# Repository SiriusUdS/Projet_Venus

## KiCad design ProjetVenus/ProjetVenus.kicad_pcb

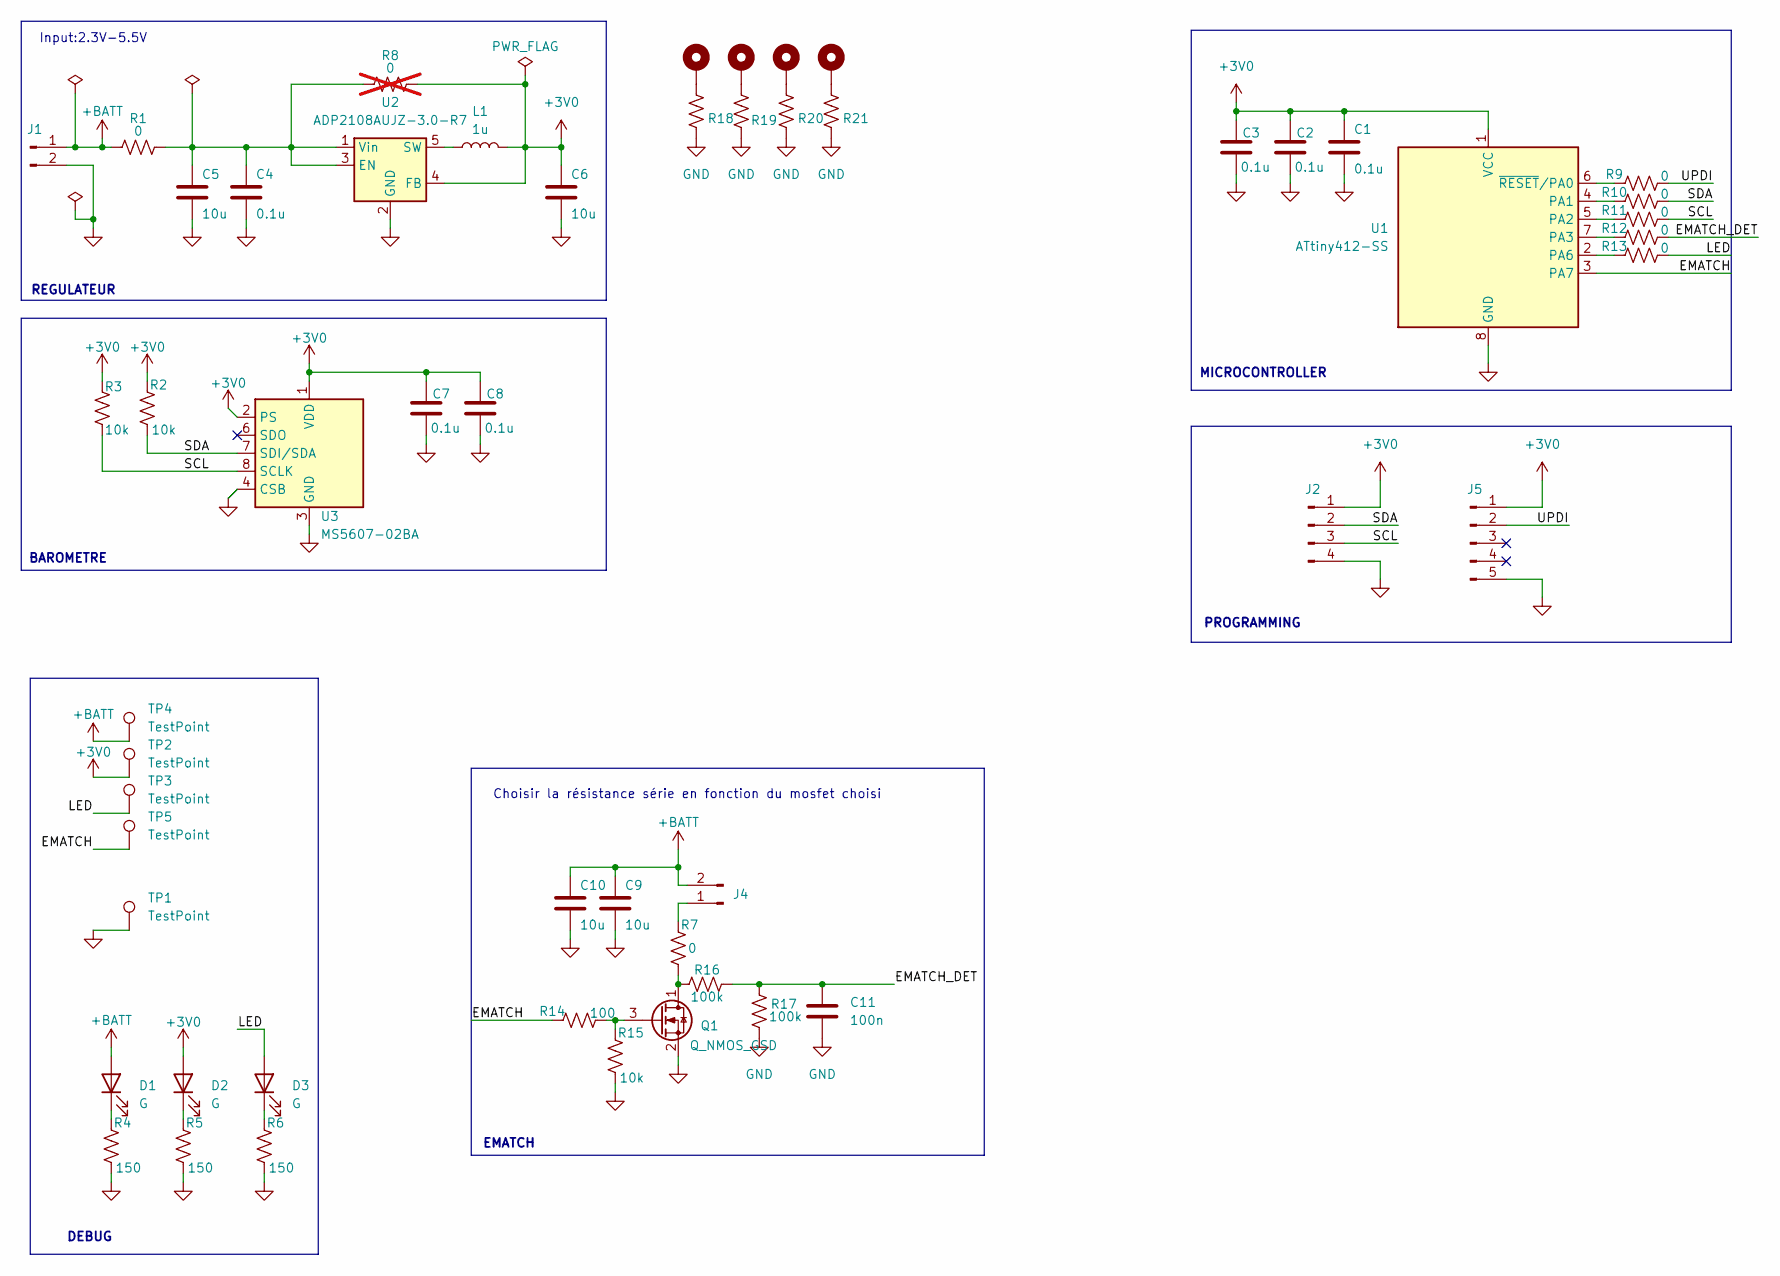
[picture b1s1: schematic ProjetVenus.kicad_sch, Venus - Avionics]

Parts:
C1, C2, C3, C4, C7, C8: 0.1u; C_0603_1608Metric
C5, C6, C9, C10: 10u; C_1206_3216Metric
C11: 100n; C_0603_1608Metric
D1, D2, D3: G; LED_0603_1608Metric
H1, H2, H3, H4: MountingHole_Pad; MountingHole_3.2mm_M3_DIN965_Pad
J1: Conn_01x02_Pin; Hirose_DF13-02P-1.25DS_1x02_P1.25mm_Horizontal
J2: Conn_01x04_Pin; PinSocket_1x04_P2.54mm_Vertical
J4: Conn_01x02_Pin; TerminalBlock_Phoenix_MKDS-1,5-2_1x02_P5.00mm_Horizontal
J5: Conn_01x05_Pin; PinSocket_1x05_P2.54mm_Vertical
L1: 1u; L_0805_2012Metric
Q1: Q_NMOS_GSD; SOT-23
R1, R9, R10, R11, R12, R13: 0; R_0805_2012Metric
R2, R3, R15: 10k; R_0603_1608Metric
R4, R5, R6: 150; R_0603_1608Metric
R7: 0; R_0603_1608Metric
R8: 0; R_0805_2012Metric; not fitted
R14: 100; R_0805_2012Metric
R16, R17: 100k; R_0603_1608Metric
R18, R19, R20, R21: R_US; R_0805_2012Metric
TP1: TestPoint; TestPoint_Pad_2.0x2.0mm
TP2, TP3, TP4, TP5: TestPoint; TestPoint_Pad_D2.0mm
U1: ATtiny412-SS; SOIC-8_3.9x4.9mm_P1.27mm
U2: ADP2108AUJZ-3.0-R7; TSOT-23-5
U3: MS5607-02BA; LGA-8_3x5mm_P1.25mm

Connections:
+3V0: C1.1, C2.1, C3.1, C6.1, C7.1, C8.1, D2.2 (A), J2.1, J5.1, L1.2, R2.2, R3.2, R8.2, TP2.1 (1_1), U1.1 (VCC), U2.4 (FB), U3.1 (VDD), U3.2 (PS)
+BATT: C9.1, C10.1, D1.2 (A), J1.1, J4.2, R1.1, TP4.1 (1_1)
/EMATCH: R14.1, TP5.1 (1_1), U1.3 (PA7)
/EMATCH_DET: C11.1, R12.2, R16.2, R17.1
/LED: D3.2 (A), R13.2, TP3.1 (1_1)
/SCL: J2.3, R3.1, R11.2, U3.8 (SCLK)
/SDA: J2.2, R2.1, R10.2, U3.7 (SDI/SDA)
/UPDI: J5.2, R9.2
GND: C1.2, C2.2, C3.2, C4.2, C5.2, C6.2, C7.2, C8.2, C9.2, C10.2, C11.2, J1.2, J2.4, J5.5, Q1.2 (S), R4.1, R5.1, R6.1, R15.1, R17.2, R18.2, R19.2, R20.2, R21.2, TP1.1 (1_1), U1.8 (GND), U2.2 (GND), U3.3 (GND), U3.4 (CSB), U3.5 (CSB)
unnamed: D1.1 (K), R4.2
unnamed: D2.1 (K), R5.2
unnamed: D3.1 (K), R6.2
unnamed: H1.1 (1_1), R18.1
unnamed: H2.1 (1_1), R19.1
unnamed: H3.1 (1_1), R20.1
unnamed: H4.1 (1_1), R21.1
unnamed: J4.1, R7.2
unnamed: Q1.1 (D), R7.1, R16.1
unnamed: Q1.3 (G), R14.2, R15.2
unnamed: R10.1, U1.4 (PA1)
unnamed: R11.1, U1.5 (PA2)
unnamed: R12.1, U1.7 (PA3)
unnamed: R13.1, U1.2 (PA6)
unnamed: R9.1, U1.6 (~RESET/PA0)
unnamed: C4.1, C5.1, R1.2, R8.1, U2.1 (Vin), U2.3 (EN)
unnamed: L1.1, U2.5 (SW)

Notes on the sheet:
Input:2.3V-5.5V
PROGRAMMING
DEBUG
MICROCONTROLLER
BAROMETRE
EMATCH
Choisir la résistance série en fonction du mosfet choisi
REGULATEUR

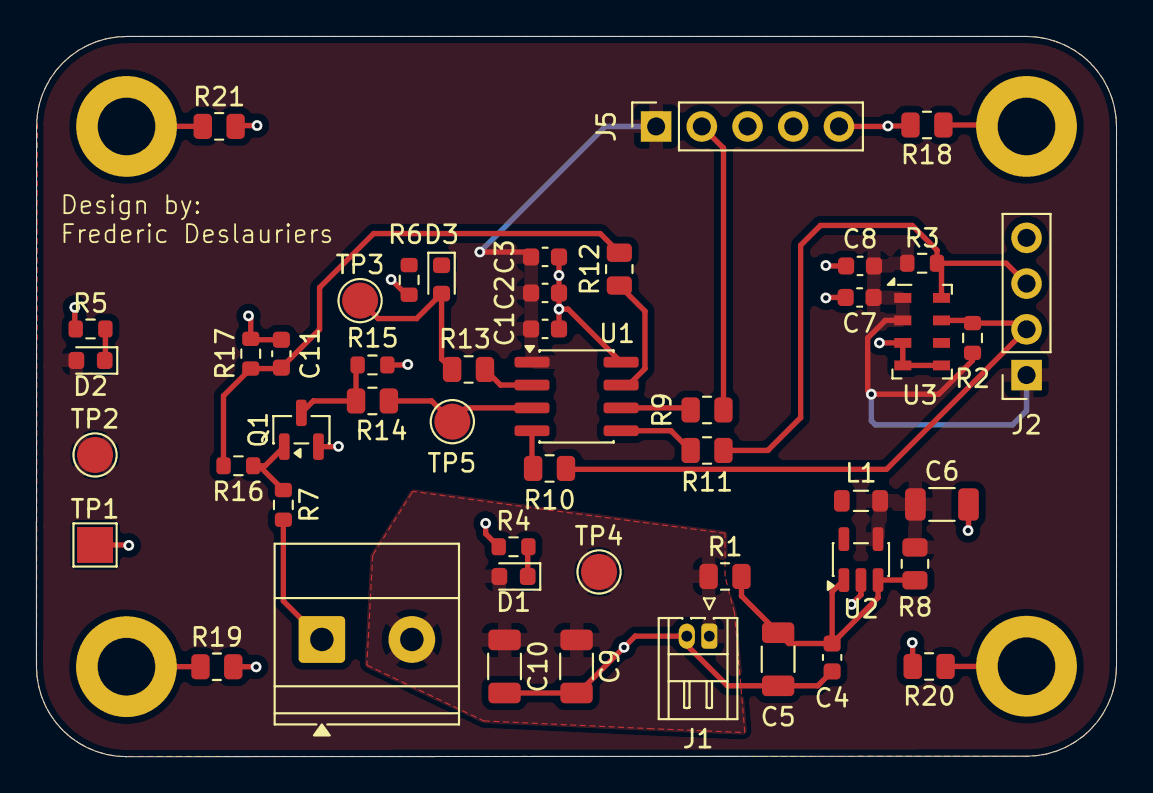
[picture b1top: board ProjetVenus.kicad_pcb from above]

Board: 2 copper layers, 60.0 x 40.0 mm, 53 parts (0 on the bottom side), 26 nets.
